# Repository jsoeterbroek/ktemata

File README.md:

## Ktemata (R6 — Default Build)

R6 is the default build. Two variants: **R6** uses a perfboard with DC5521 charge management, and **R6 PCH** uses a custom power/charge carrier board. Both keep Wikipedia, maps and Gutenberg when power and networking are gone.

---

### R6 Perfboard Variant

The base R6 variant uses a flat perfboard for cost-effectiveness and rapid iteration. The DC5521 charge path feeds the Waveshare UPS Module 3S directly, eliminating the need for a separate carrier board while maintaining the rugged Peli 1200 enclosure design.

#### Target Hardware

- **Host Case:** Peli 1200 (rugged, IP67-rated)
- **Computer:** Raspberry Pi 5 (4 GB)
- **Display:** Waveshare 7" DSI LCD (C)
- **Keyboard:** Rii K06 Touch Keyboard
- **Storage:** NVMe SSD
- **Power:** Waveshare UPS Module 3S with three 18650 cells in 3S

#### Features

- Built-in Ktemata Admin at `:8081` for storage, library, power and AI
- UPS INA219 telemetry read by the Pi
- Wikipedia, maps, and Gutenberg content preservation
- Offline library access without networking

---

### R6 PCH Variant

The R6 PCH (Power/Charge Hub) variant uses a custom 63 × 66 mm two-layer carrier board for the UPS Module 3S, charge input and sense routing. It does not carry a separate microcontroller or display.

#### Target Hardware

- **Host Case:** Peli 1200 (rugged, IP67-rated)
- **Computer:** Raspberry Pi 5 (4 GB)
- **Display:** Waveshare 7" DSI LCD (C)
- **Keyboard:** Rii K06 Touch Keyboard
- **Storage:** NVMe SSD
- **Power:** UPS Module 3S with three 18650 cells

#### Features

- UPS Module 3S (3S 2×4 configuration) with integrated protection
- Charge-input routing and 12.6 V / 2 A input
- I²C routing for the UPS INA219
- Modular carrier for power and charge connections

#### Design Highlights

- **Power Management:** 12.6 V charge input and UPS carrier
- **I²C Integration:** INA219 routed to the Pi
- **Modular Design:** the carrier is serviceable without opening the case

---

### Build Instructions

#### Basic Setup

```bash
git clone https://github.com/jsoeterbroek/ktemata.git
cd ktemata
python3 -m venv .venv
source .venv/bin/activate
pip install -r packages.txt
```

#### Build Variants

1. **R6 (Perfboard)** — lower cost, faster iteration
2. **R6 PCH** — custom power/charge carrier

```bash
python3 cad/tools/export.py --variant R6_PERFBOARD
python3 cad/tools/export.py --variant R6_PCH
```

---

### Documentation

- [`docs/R6.md`](docs/R6.md) — R6 hardware and CAD specifications
- [`cad/kicad/r6/README.md`](cad/kicad/r6/README.md) — KiCad design rules and board documentation
- [`work/scripts/check_r6.sh`](work/scripts/check_r6.sh) — interference check script for R6 variants

---

### License

[Add license information here]

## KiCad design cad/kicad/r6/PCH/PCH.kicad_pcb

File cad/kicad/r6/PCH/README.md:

## Power / charge carrier board (PCH)

The PCH is the r6's 12.6 V power pass-through: a single-sheet, 63 × 66 mm two-layer board with no
conversion, protection or controller. It carries the Waveshare UPS Module 3S 2×4 header, the UPS
12.6 V branch in and the 12.6 V auxiliary output. The R6 status controller, its display and its
button are not part of this board or project.

Nets and pins are in [`PCH.kicad_sch`](PCH.kicad_sch); assembly practice is in
[`docs/WIRING.md`](../../../../docs/WIRING.md) §3.

| Connector | Pads | Nets | Job |
|---|---|---|---|
| J5 `UPS3S_HDR_2X4` | 8 | 5/6 `GND`, 7/8 `+5V`; 1–4 no-connect | UPS Module 3S 2×4 header. The UPS I²C pair and both 3V3 pins are deliberately open: nothing on the R6 PCH consumes them |
| J7 `UPS_12V6_IN` | 2 | 1 `BAT_12V6_OUT`, 2 `GND` | UPS 12.6 V branch in |
| J8 `AUX_12V6_OUT` | 2 | 1 `BAT_12V6_OUT`, 2 `GND` | same net as J7 — feed-through 12.6 V aux outlet (unused in the current build) |

The only components on the board are those three connectors and four M2.5 mounting holes. There is
no active part, no clock and no I/O beyond the two power connectors and the UPS header.

The supplied DC5521 charge lead and self-lock button plug directly into the UPS; neither is routed
through the PCH. No charge current passes through the board.

## Deliberately not on this board

- **No fuse.** The UPS Module 3S protects the in-module pack; a pack built outside it carries its
  own fuse in the pack's positive lead (`docs/WIRING.md` §2).
- **No charge-sense divider.** The sense tap and its 47k/10k/100 nF filter were removed together
  with the status controller; nothing on R6 measures the charge input.
- **No controller, display, button or status clock.** The R6 status subsystem was removed from the
  hardware.
- **No Pi or display power.** The Pi 5 and the 7-inch panel stay on the UPS's own USB-C lead
  (`docs/WIRING.md` §2).

## Checks and build files

```bash
kicad-cli sch erc --severity-all -o /tmp/pch_erc.rpt PCH.kicad_sch   # 0 errors
kicad-cli pcb drc --severity-all -o DRC.rpt PCH.kicad_pcb            # 0 violations, 0 unconnected
```

The exported netlist is [`PCH.net`](PCH.net); the parts list is [`PCH.csv`](PCH.csv); fabrication
data is in [`gerbers/`](gerbers/). ERC reports only `lib_symbol_mismatch` warnings because the
project symbols are embedded in the schematic.

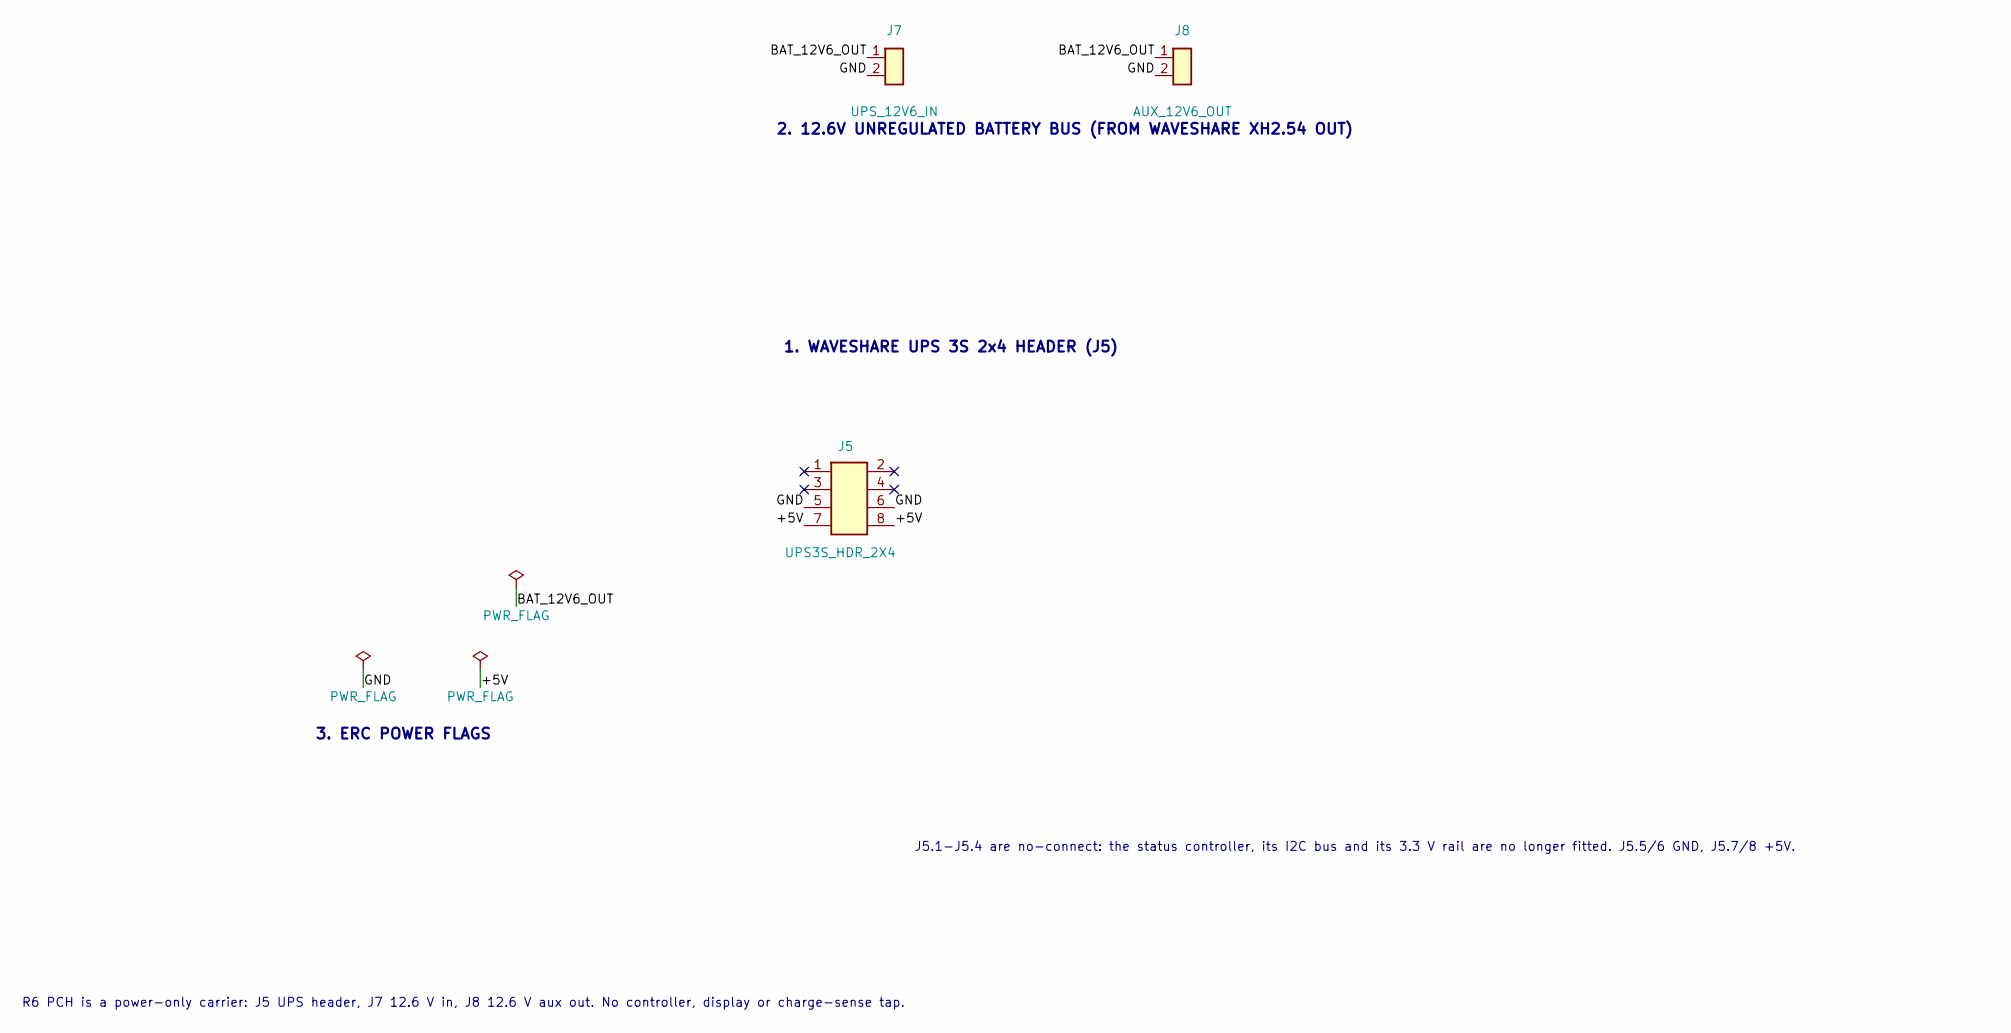
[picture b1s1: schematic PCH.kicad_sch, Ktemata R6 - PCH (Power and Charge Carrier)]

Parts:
J5: UPS3S_HDR_2X4; PinHeader_2x04_P2.54mm_Vertical
J7: UPS_12V6_IN; JST_XH_B2B-XH-A_1x02_P2.50mm_Vertical
J8: AUX_12V6_OUT; JST_XH_B2B-XH-A_1x02_P2.50mm_Vertical

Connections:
/+5V: J5.7, J5.8
/BAT_12V6_OUT: J7.1, J8.1
/GND: J5.5, J5.6, J7.2, J8.2

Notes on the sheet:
1. WAVESHARE UPS 3S 2x4 HEADER (J5)
J5.1-J5.4 are no-connect: the status controller, its I2C bus and its 3.3 V rail are no longer fitted. J5.5/6 GND, J5.7/8 +5V.
2. 12.6V UNREGULATED BATTERY BUS (FROM WAVESHARE XH2.54 OUT)
3. ERC POWER FLAGS
R6 PCH is a power-only carrier: J5 UPS header, J7 12.6 V in, J8 12.6 V aux out. No controller, display or charge-sense tap.

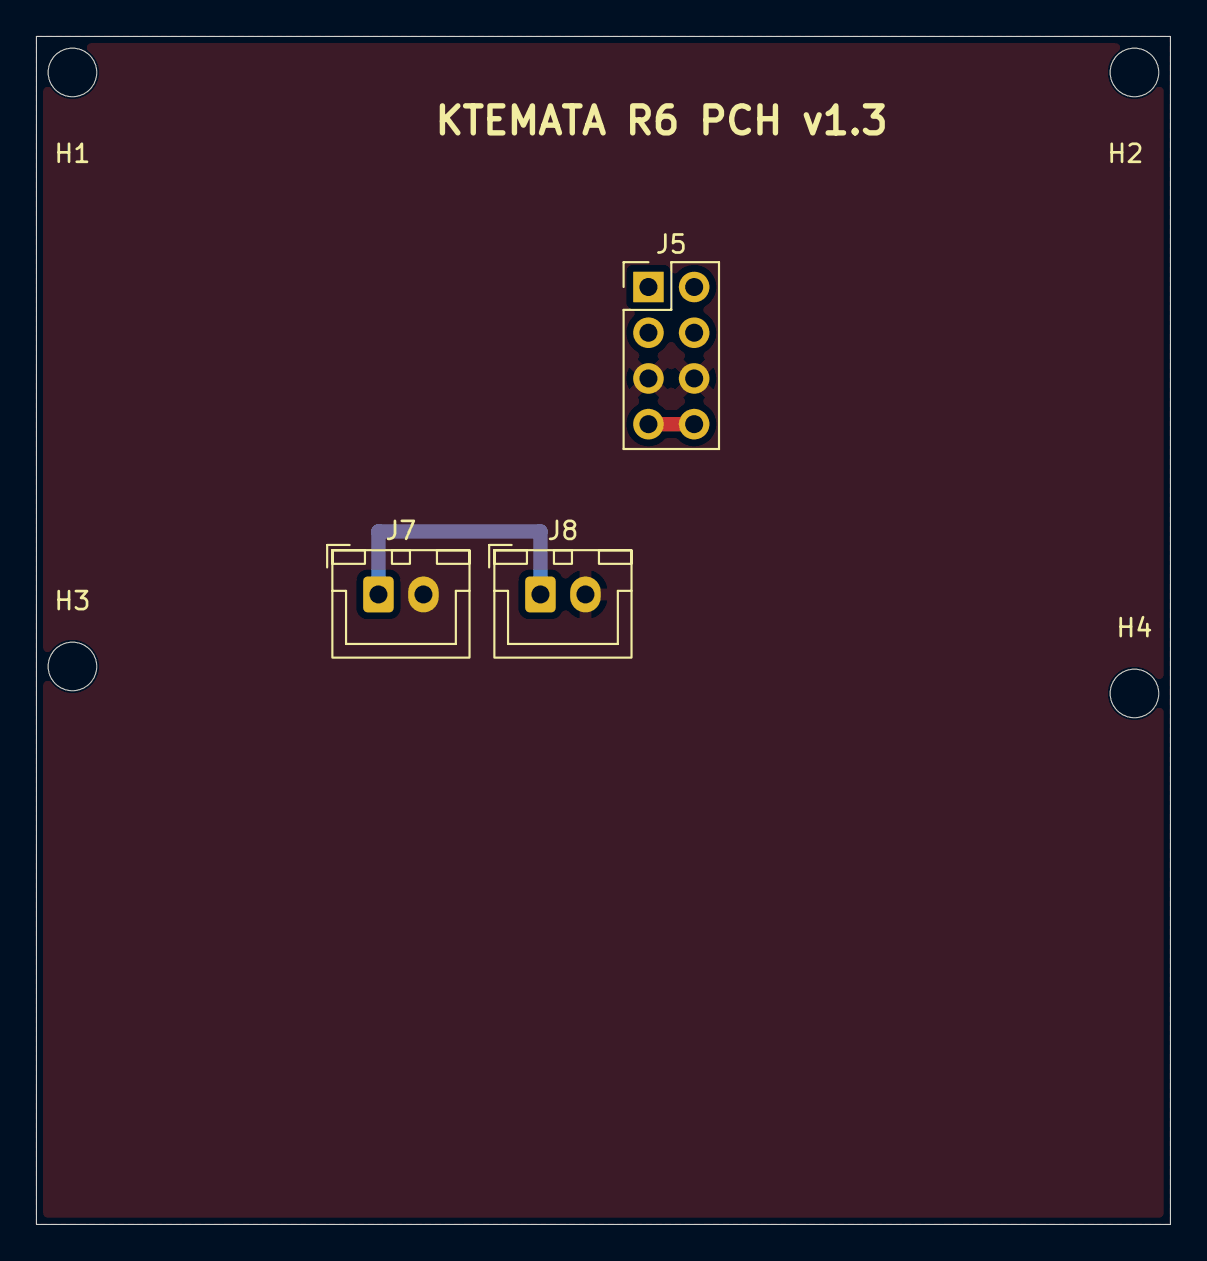
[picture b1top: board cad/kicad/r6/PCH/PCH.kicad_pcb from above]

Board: 2 copper layers, 63.0 x 66.0 mm, 7 parts (0 on the bottom side), 3 nets.

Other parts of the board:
H1, H2, H3, H4: MountingHole_2.7mm_M2.5

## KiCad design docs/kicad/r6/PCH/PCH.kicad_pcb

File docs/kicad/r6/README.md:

# KiCad 10.0

## CLI
Use the cli to edit, create kicad files, kicad-cli location:
/Applications/KiCad/KiCad.app/Contents/MacOS/kicad-cli

## Design rules check
Check design rules after each edit, eg.:
/Applications/KiCad/KiCad.app/Contents/MacOS/kicad-cli pcb drc PCH/PCH.kicad_pcb

# Power Distribution & Communication Hub (PCH) carrier board

The PCH is the r6's **passive** 12.6 V / aux-rail / I2C hub: a single-sheet, 50 × 50 mm two-layer
board with no conversion, no protection and no active parts. Nets and pins are in
[`PCH.kicad_pro`](PCH/PCH.kicad_pro); assembly practice is [`../../WIRING.md`](../../WIRING.md) §4.

| Connector | Pads | Nets | Job |
|---|---|---|---|
| J1 `DC-099_12V6_IN` | 2 | `CHG_12V6_IN`, `GND` | 12.6 V charge input from the panel-jack harness |
| J2 `UPS_12V6_CHG_OUT` | 2 | `CHG_12V6_IN`, `GND` | same net as J1 — feed-through to the UPS Module 3S charge input |
| J3 `SW16_LATCH_LED` | 4 | `UPS_SW_1`, `UPS_SW_2`, `SW_LED_ANODE`, `GND` | 16 mm latching switch: contacts on 1/2, its LED on 3/4 |
| J4 `UPS_SW_EN` | 2 | `UPS_SW_1`, `UPS_SW_2` | the same two switch nets on a second outlet — fit the switch to J3 **or** J4, never both |
| J5 `UPS3S_HDR_2X4` | 8 | `I2C_SCL`, `I2C_SDA`, `+3V3` ×2, `GND` ×2, `+5V` ×2 | UPS Module 3S interface |
| J6 `HOST_AUX_PWR_I2C` | 5 | `I2C_SCL`, `I2C_SDA`, `+3V3`, `GND`, `+5V` | status side: FireBeetle, RTC, OLED |
| J7 `UPS_12V6_IN` | 2 | `BAT_12V6_OUT`, `GND` | UPS 12.6 V branch in |
| J8 `AUX_12V6_OUT` | 2 | `BAT_12V6_OUT`, `GND` | same net as J7 — feed-through 12.6 V aux outlet |
| R1 `330R` | 2 | `+5V`, `SW_LED_ANODE` | switch LED current from the aux 5 V rail, ≈9 mA |

The LED therefore shows that the aux rail is live, not the switch position.

## Deliberately not on this board

- **No fuse.** The UPS Module 3S protects the in-module pack; a pack built outside it carries its
  own fuse in the pack's positive lead (WIRING §4.4).
- **No charge-sense divider.** The 47k / 10k + 100 nF divider (12.6 V → 2.21 V at 221 µA) is BOM
  item 20a, soldered inline, and appears on the r6 `/Power` sheet as the `J5` block — not here.
- **No Pi or display power.** The PCH's 5 V and 3.3 V feed the status side only; the Pi 5 and the
  7-inch panel stay on the UPS's own USB-C lead (WIRING §4.2).
- **No PCIe or USB connector.** The NVMe Base Duo and the K06 dongle connect to the Pi directly.

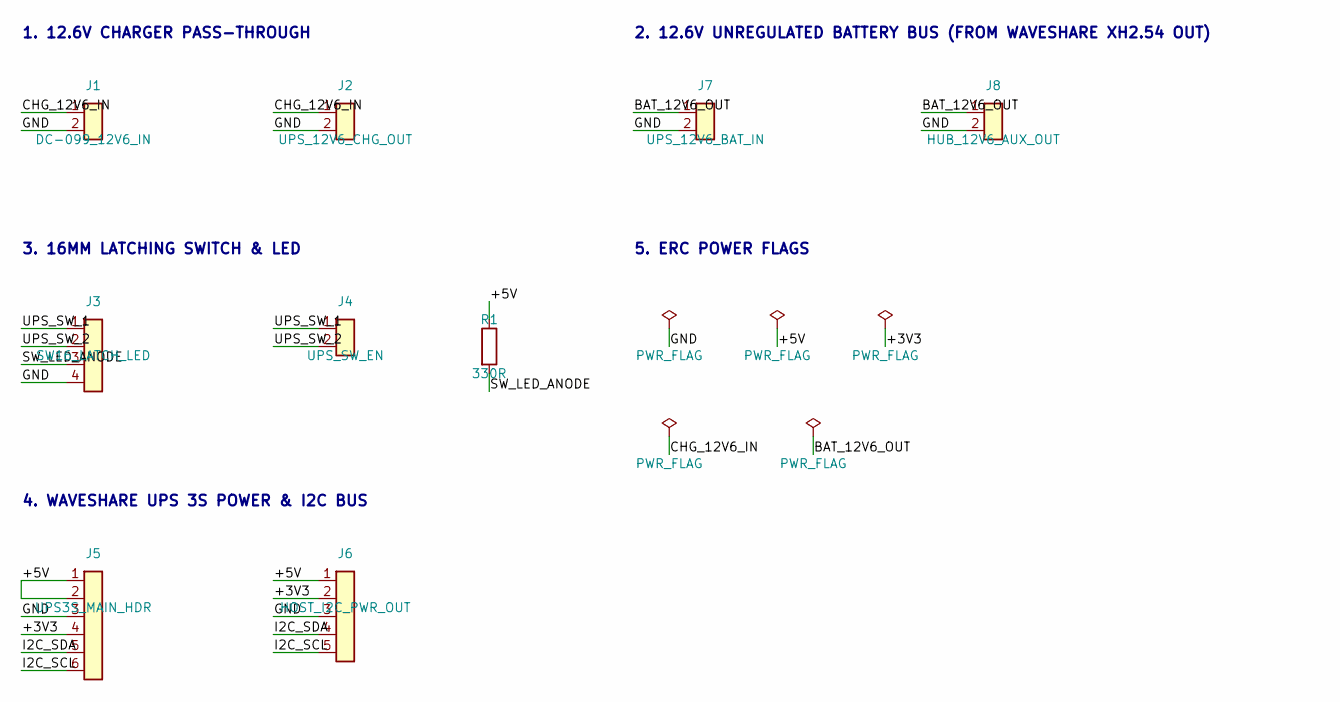
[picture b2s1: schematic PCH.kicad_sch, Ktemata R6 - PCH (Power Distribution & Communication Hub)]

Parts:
J1: DC-099_12V6_IN; JST_XH_B2B-XH-A_1x02_P2.50mm_Vertical
J2: UPS_12V6_CHG_OUT; JST_XH_B2B-XH-A_1x02_P2.50mm_Vertical
J3: SW16_LATCH_LED; JST_XH_B4B-XH-A_1x04_P2.50mm_Vertical
J4: UPS_SW_EN; JST_XH_B2B-XH-A_1x02_P2.50mm_Vertical
J5: UPS3S_MAIN_HDR; PinHeader_1x06_P2.54mm_Vertical
J6: HOST_I2C_PWR_OUT; PinHeader_1x05_P2.54mm_Vertical
J7: UPS_12V6_BAT_IN; JST_XH_B2B-XH-A_1x02_P2.50mm_Vertical
J8: HUB_12V6_AUX_OUT; JST_XH_B2B-XH-A_1x02_P2.50mm_Vertical
R1: 330R; R_0603_1608Metric

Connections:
/+3V3: J5.4, J6.2
/+5V: J5.1, J5.2, J6.1, R1.1
/BAT_12V6_OUT: J7.1, J8.1
/CHG_12V6_IN: J1.1, J2.1
/GND: J1.2, J2.2, J3.4, J5.3, J6.3, J7.2, J8.2
/I2C_SCL: J5.6, J6.5
/I2C_SDA: J5.5, J6.4
/SW_LED_ANODE: J3.3, R1.2
/UPS_SW_1: J3.1, J4.1
/UPS_SW_2: J3.2, J4.2

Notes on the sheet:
1. 12.6V CHARGER PASS-THROUGH
3. 16MM LATCHING SWITCH & LED
4. WAVESHARE UPS 3S POWER & I2C BUS
5. ERC POWER FLAGS
2. 12.6V UNREGULATED BATTERY BUS (FROM WAVESHARE XH2.54 OUT)

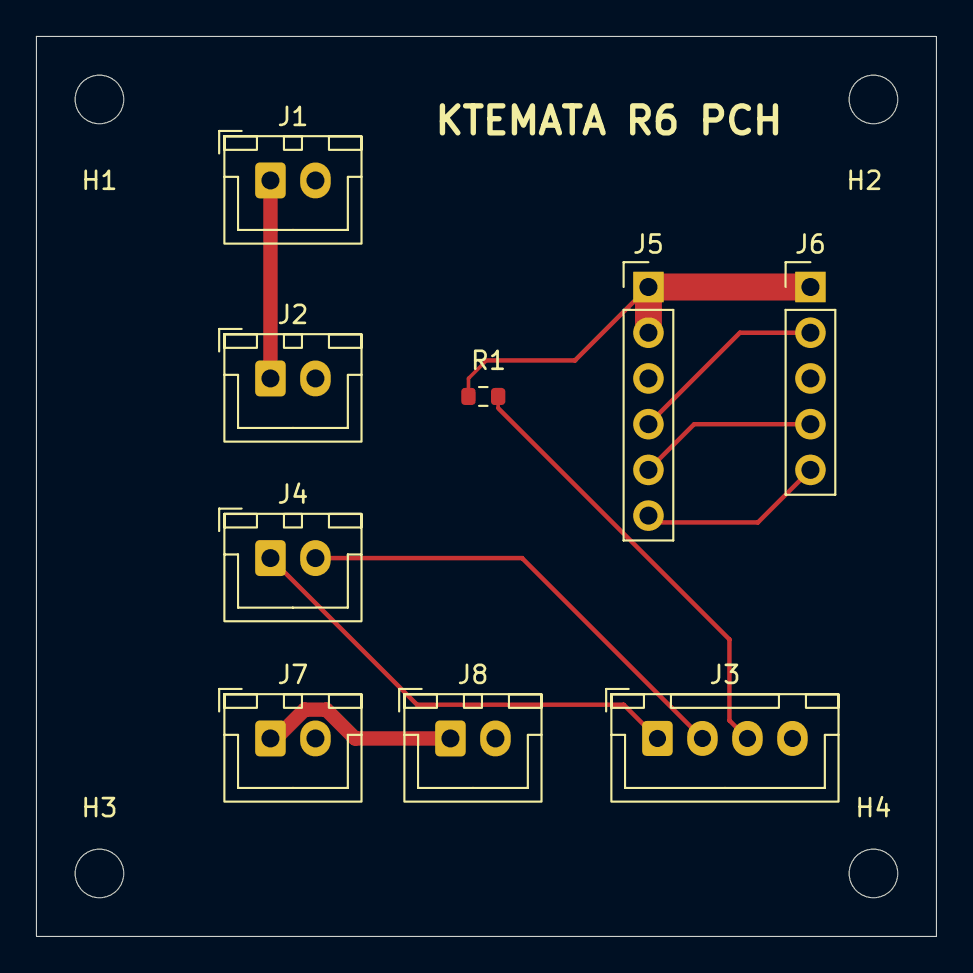
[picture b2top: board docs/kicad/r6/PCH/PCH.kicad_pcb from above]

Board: 2 copper layers, 50.0 x 50.0 mm, 13 parts (0 on the bottom side), 10 nets.

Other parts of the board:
H1, H2, H3, H4: MountingHole_2.7mm_M2.5
